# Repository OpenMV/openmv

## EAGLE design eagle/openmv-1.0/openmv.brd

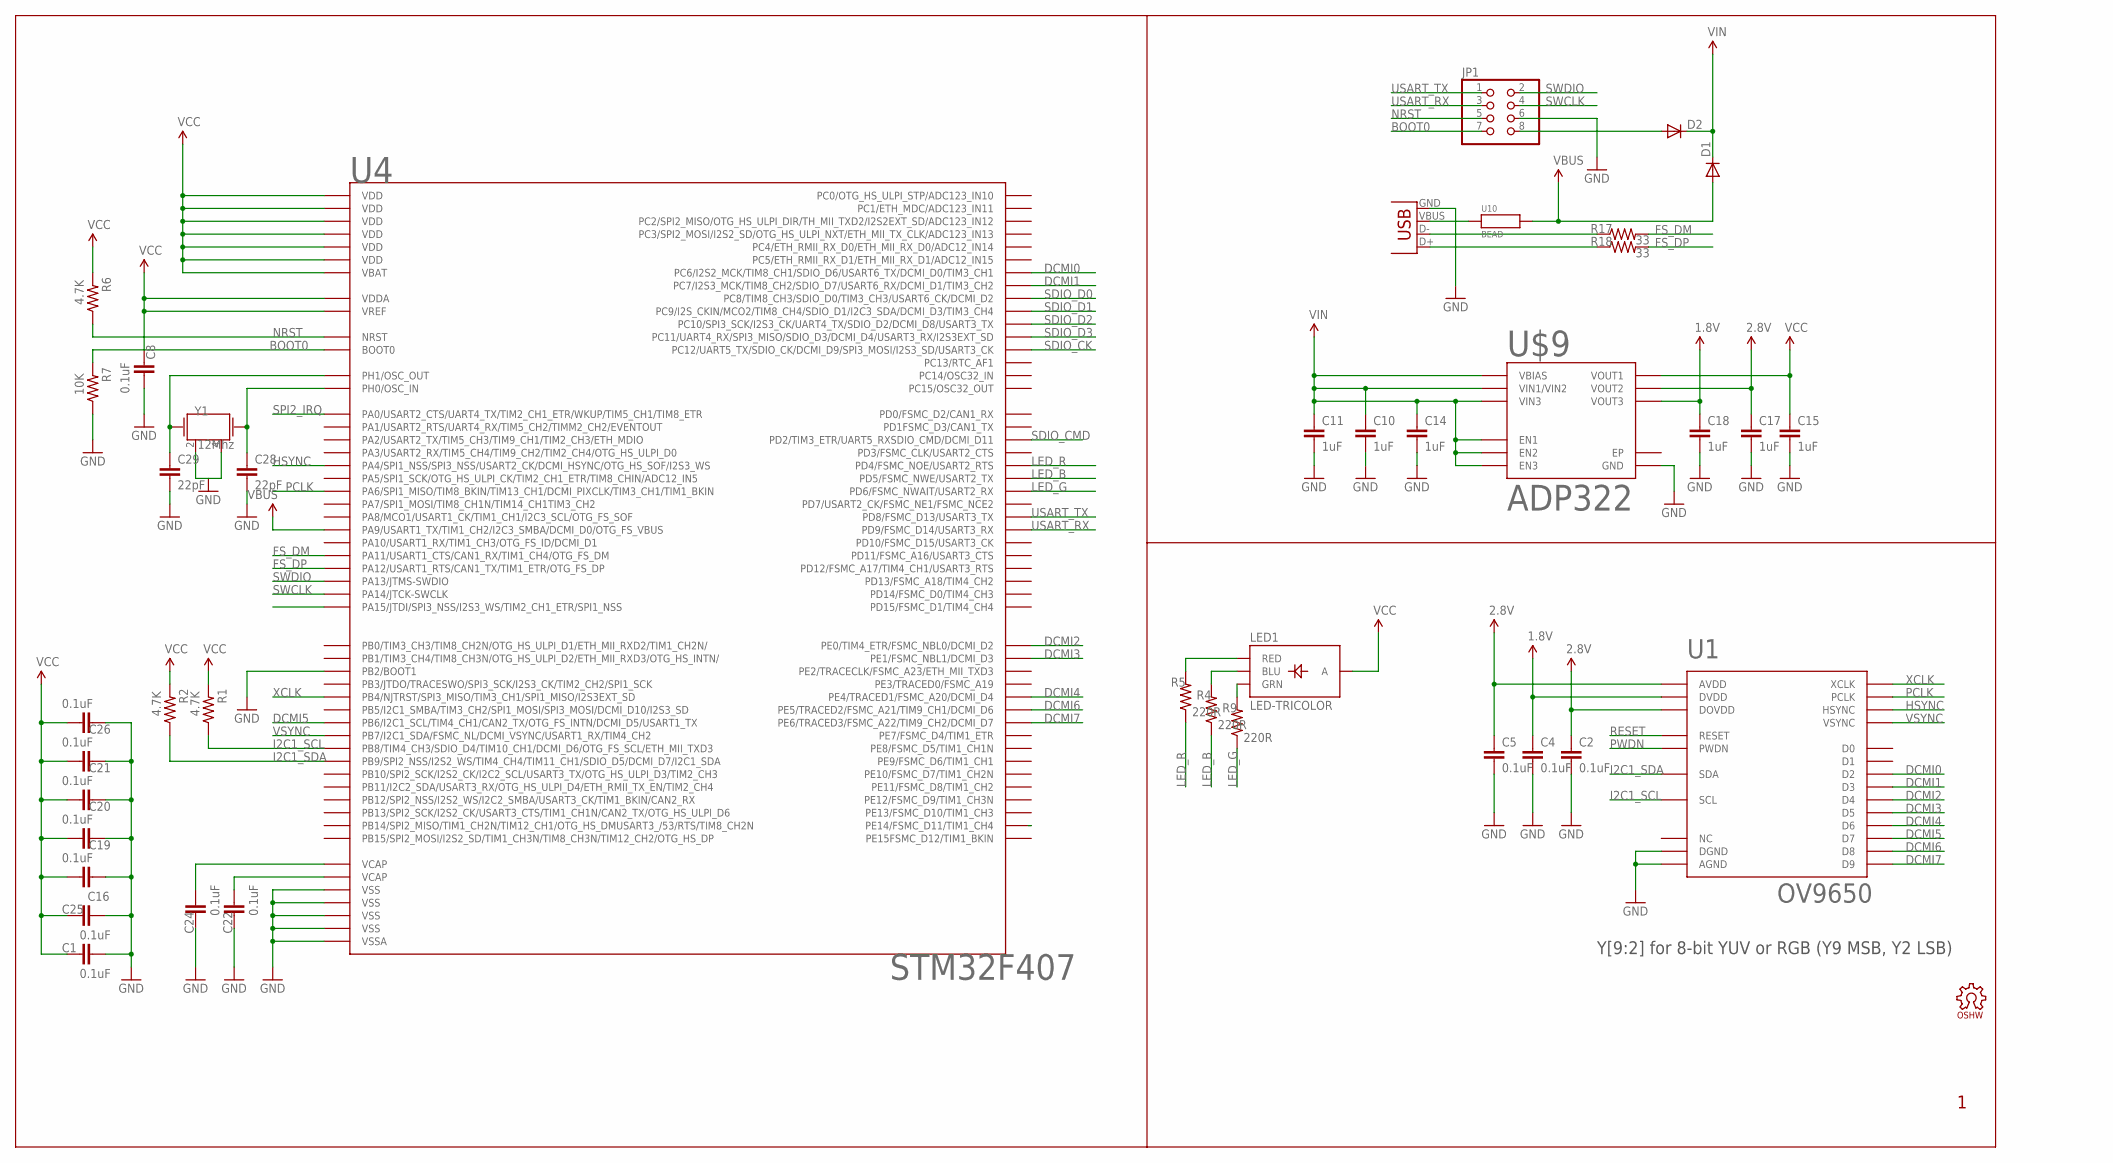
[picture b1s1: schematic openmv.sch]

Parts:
C1, C2, C4, C5, C8, C16, C19, C20, C21, C22, C24, C25, C26: 0.1uF; 0402-CAP
C10, C11, C14, C15, C17, C18: 1uF; 0402-CAP
C28, C29: 22pF; 0402-CAP
D1, D2: DIODESOD; SOD-323
JP1: PINHD-2X4; 2X04
LED1: LED-TRICOLOR; LED-TRICOLOR-SMD
LOGO2: OSHW_LOGO_FILLX0100-NT; OSHW_FILLX100_NOTEXT
R1, R2, R6: 4.7K; 0402-RES
R4, R5, R9: 220R; 0402-RES
R7: 10K; 0402-RES
R17, R18: 33; 0402-RES
U1: OV9650
U4: STM32F407; LQFP100
U10: BEAD; 0402-CAP
U$9: ADP322; WFQFN-16
X2: USB-MICROB
Y1: 12Mhz; CRYSTAL-SMD-5X3

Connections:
1.8V: C4.1, C18.1, U1.P$10 (DVDD), U$9.8 (VOUT3)
2.8V: C2.1, C5.1, C17.1, U1.P$4 (AVDD), U1.P$11 (DOVDD), U$9.6 (VOUT2)
BOOT0: JP1.7, R7.2, U4.94 (BOOT0)
DCMI0: U1.P$19 (D2), U4.63 (PC6/I2S2_MCK/TIM8_CH1/SDIO_D6/USART6_TX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)
DCMI1: U1.P$21 (D3), U4.64 (PC7/I2S3_MCK/TIM8_CH2/SDIO_D7/USART6_RX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)
DCMI2: U1.P$22 (D4), U4.97 (PE0/TIM4_ETR/FSMC_NBL0/DCMI_D2)
DCMI3: U1.P$20 (D5), U4.98 (PE1/FSMC_NBL1/DCMI_D3)
DCMI4: U1.P$18 (D6), U4.3 (PE4/TRACED1/FSMC_A20/DCMI_D4)
DCMI5: U1.P$16 (D7), U4.92 (PB6/I2C1_SCL/TIM4_CH1/CAN2_TX/OTG_FS_IN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)
DCMI6: U1.P$14 (D8), U4.4 (PE5/TRACED2/FSMC_A21/TIM9_CH1/DCMI_D6)
DCMI7: U1.P$12 (D9), U4.5 (PE6/TRACED3/FSMC_A22/TIM9_CH2/DCMI_D7)
FS_DM: R17.2, U4.70 (PA11/USART1_CTS/CAN1_RX/TIM1_CH4/OTG_FS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)
FS_DP: R18.2, U4.71 (PA12/USART1_RTS/CAN1_TX/TIM1_ETR/OTG_FS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)
GND: C1.1, C2.2, C4.2, C5.2, C8.1, C10.2, C11.2, C14.2, C15.2, C16.1, C17.2, C18.2, C19.2, C20.2, C21.2, C22.2, C24.2, C25.1, C26.2, C28.2, C29.2, JP1.6, R7.1, U1.P$2 (AGND), U1.P$15 (DGND), U4.10 (VSS), U4.20 (VSSA), U4.27 (VSS), U4.37 (PB2/BOOT1), U4.74 (VSS), U4.99 (VSS), U$9.12 (GND), X2.GND, Y1.2, Y1.4
HSYNC: U1.P$9 (HSYNC), U4.29 (PA4/SPI1_NSS/SPI3_NSS/USART2_CK/DCMI_HS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)
I2C1_SCL: R1.1, U1.P$5 (SCL), U4.95 (PB8/TIM4_CH3/SDIO_D4/TIM10_CH1/DCMI_D6/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)
I2C1_SDA: R2.1, U1.P$3 (SDA), U4.96 (PB9/SPI2_NSS/I2S2_WS/TIM4_CH4/TIM11_CH1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)
LED_B: R4.1, U4.86 (PD5/FSMC_NWE/USART2_TX)
LED_G: R9.1, U4.87 (PD6/FSMC_NWAIT/USART2_RX)
LED_R: R5.1, U4.85 (PD4/FSMC_NOE/USART2_RTS)
unnamed: D2.2 (A), JP1.8
unnamed: LED1.G (GRN), R9.2
unnamed: LED1.B (BLU), R4.2
unnamed: C29.1, U4.13 (PH1/OSC_OUT), Y1.1
unnamed: C28.1, U4.12 (PH0/OSC_IN), Y1.3 (2)
unnamed: LED1.R (RED), R5.2
unnamed: R17.1, X2.D-
unnamed: R18.1, X2.D+
unnamed: U10.1, X2.VBUS
NRST: JP1.5, R6.1, U4.14 (NRST)
PCLK: U1.P$17 (PCLK), U4.31 (PA6/SPI1_MISO/TIM8_BKIN/TIM13_CH1/DCMI_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)
PWDN: U1.P$8 (PWDN)
RESET: U1.P$6 (RESET)
SDIO_CK: U4.80 (PC12/UART5_TX/SDIO_CK/DCMI_D9/SPI3_MOSI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)
SDIO_CMD: U4.83 (PD2/TIM3_ETR/UART5_RXSDIO_CMD/DCMI_D11)
SDIO_D0: U4.65 (PC8/TIM8_CH3/SDIO_D0/TIM3_CH3/USART6_CK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)
SDIO_D1: U4.66 (PC9/I2S_CKIN/MCO2/TIM8_CH4/SDIO_D1/I2C3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)
SDIO_D2: U4.78 (PC10/SPI3_SCK/I2S3_CK/UART4_TX/SDIO_D2/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)
SDIO_D3: U4.79 (PC11/UART4_RX/SPI3_MISO/SDIO_D3/DCMI_D4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)
SPI2_IRQ: U4.23 (PA0/USART2_CTS/UART4_TX/TIM2_CH1_ETR/WK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)
SWCLK: JP1.4, U4.76 (PA14/JTCK-SWCLK)
SWDIO: JP1.2, U4.72 (PA13/JTMS-SWDIO)
USART_RX: JP1.3, U4.56 (PD9/FSMC_D14/USART3_RX)
USART_TX: JP1.1, U4.55 (PD8/FSMC_D13/USART3_TX)
VBUS: D1.2 (A), U4.68 (PA9/USART1_TX/TIM1_CH2/I2C3_SMBA/DCMI_D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), U10.2
VCAP1: C24.1, U4.49 (VCAP)
VCAP2: C22.1, U4.73 (VCAP)
VCC: C1.2, C8.2, C15.1, C16.2, C19.1, C20.1, C21.1, C25.2, C26.1, LED1.A, R1.2, R2.2, R6.2, U4.6 (VBAT), U4.11 (VDD), U4.19 (VDD), U4.21 (VREF), U4.22 (VDDA), U4.28 (VDD), U4.50 (VDD), U4.75 (VDD), U4.100 (VDD), U$9.5 (VOUT1)
VIN: C10.1, C11.1, C14.1, D1.1 (C), D2.1 (C), U$9.1 (EN1), U$9.2 (VBIAS), U$9.3 (VIN1/VIN2), U$9.10 (VIN3), U$9.15 (EN3), U$9.16 (EN2)
VSYNC: U1.P$7 (VSYNC), U4.93 (PB7/I2C1_SDA/FSMC_NL/DCMI_VSYNC/USART1_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)
XCLK: U1.P$13 (XCLK), U4.90 (PB4/NJTRST/SPI3_MISO/TIM3_CH1/SPI1_MISO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)

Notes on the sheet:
Y[9:2] for 8-bit YUV or RGB (Y9 MSB, Y2 LSB)

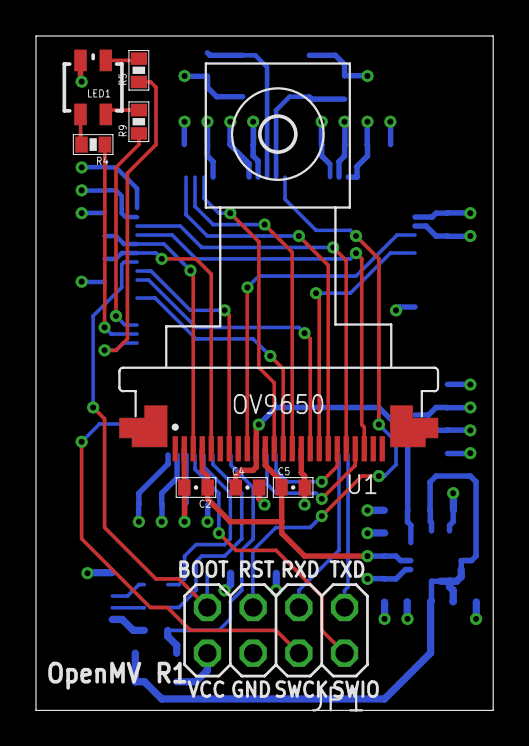
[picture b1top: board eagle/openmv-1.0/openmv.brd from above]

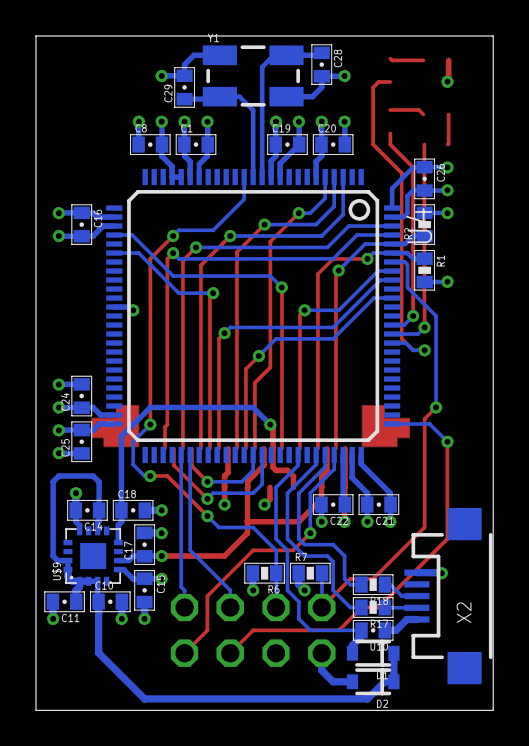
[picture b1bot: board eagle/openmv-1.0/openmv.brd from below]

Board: 4 copper layers, 25.4 x 37.5 mm, 41 parts (31 on the bottom side), 42 nets.

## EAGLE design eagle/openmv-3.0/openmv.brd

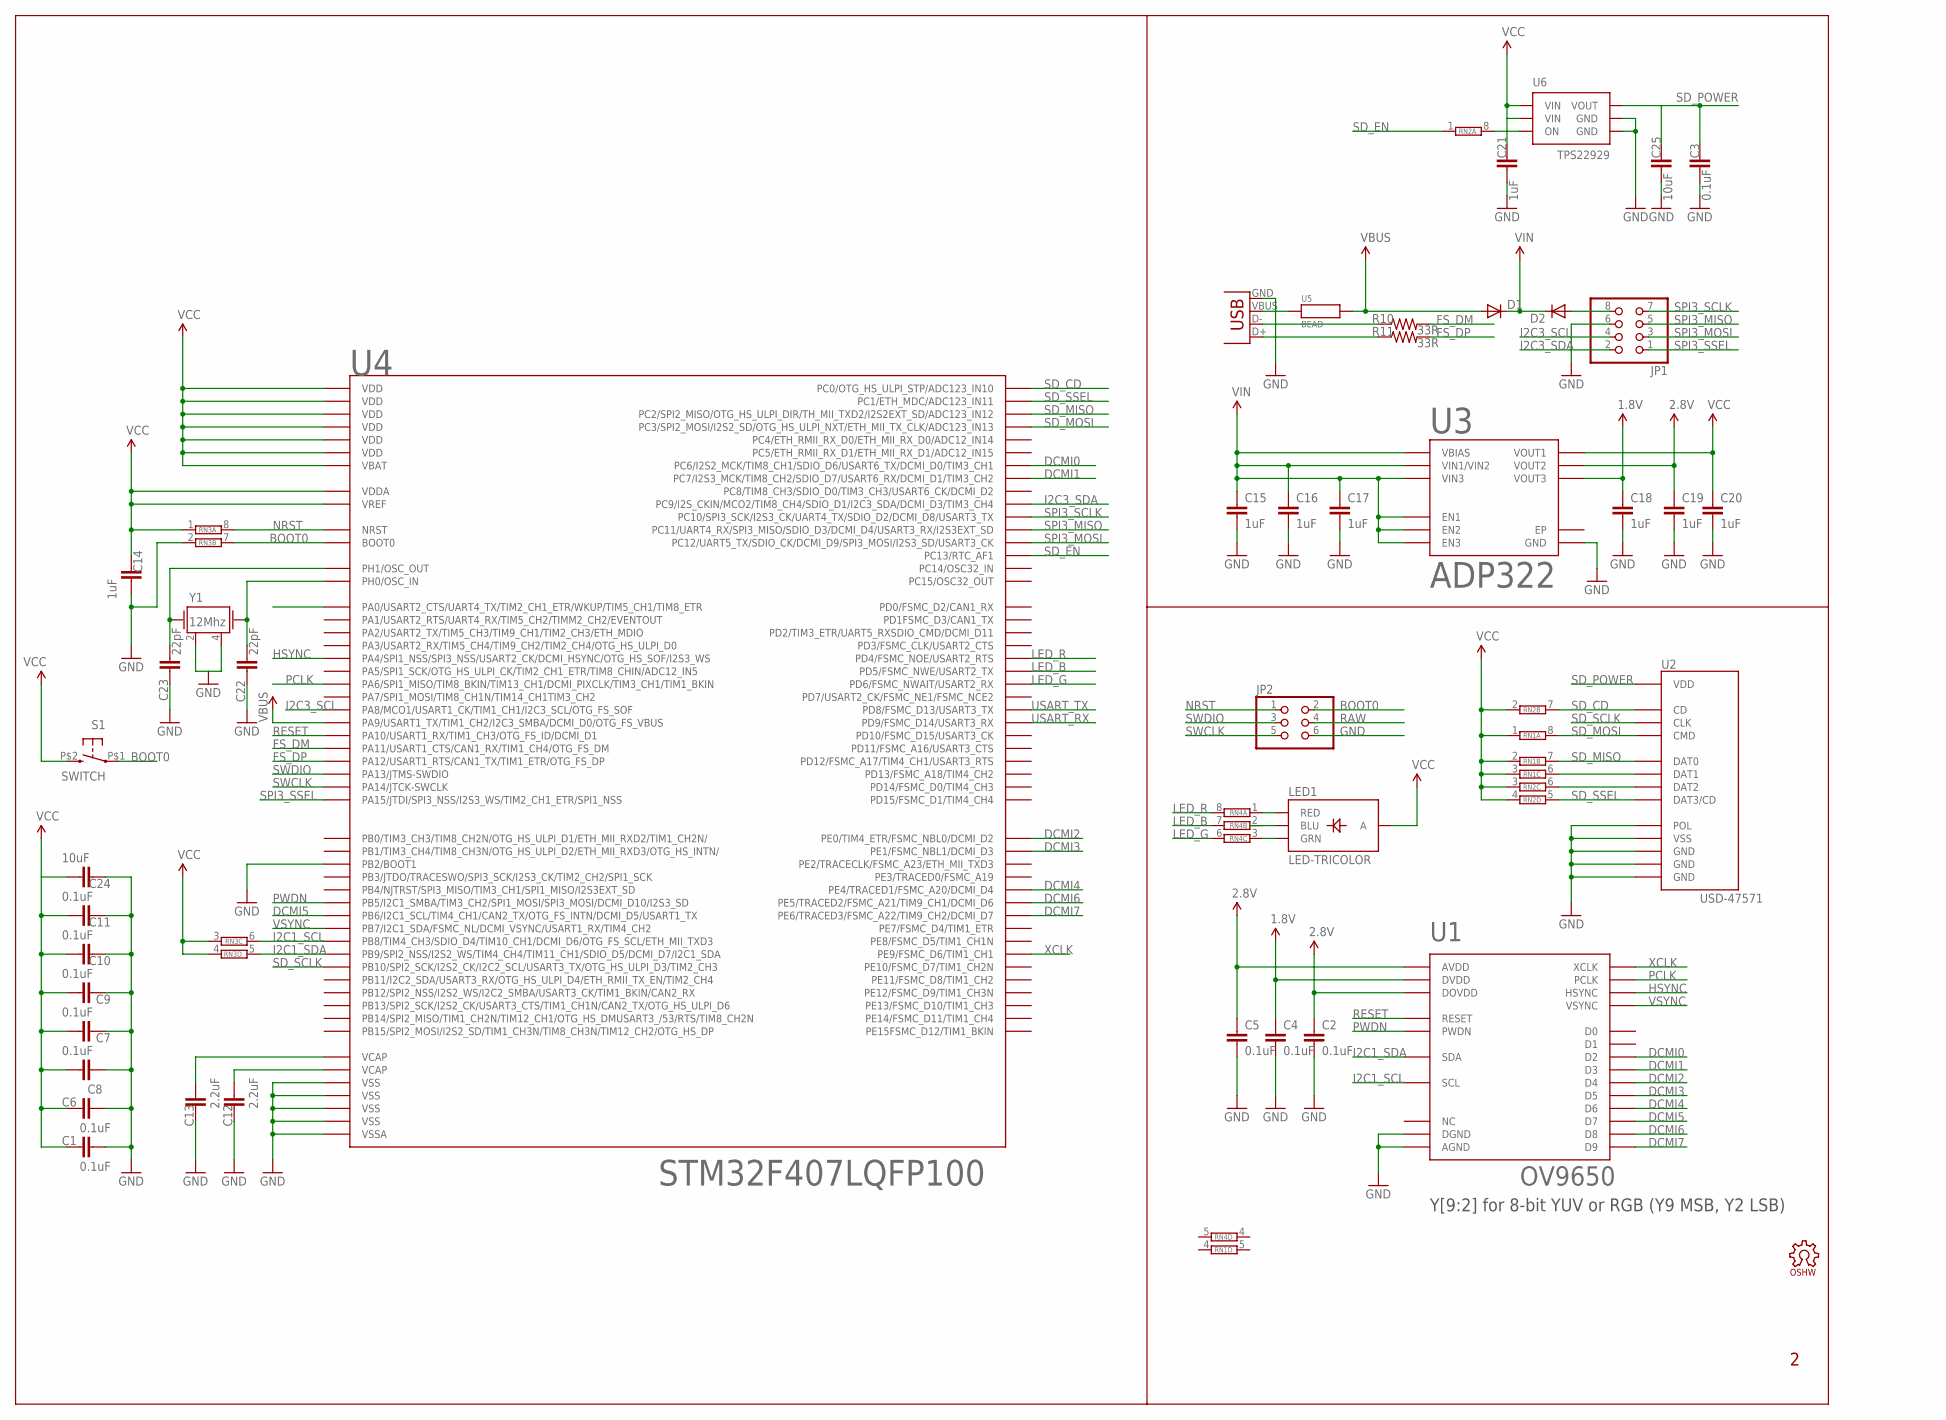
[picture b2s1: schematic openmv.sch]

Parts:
C1, C2, C3, C4, C5, C6, C7, C8, C9, C10, C11: 0.1uF; 0402-CAP
C12, C13: 2.2uF; 0402-CAP
C14, C15, C16, C17, C18, C19, C20, C21: 1uF; 0402-CAP
C22, C23: 22pF; 0402-CAP
C24, C25: 10uF; 0805
D1, D2: DIODESOD; SOD-323
JP1: PINHD-2X4; 2X04
JP2: PINHD-2X3; 2X03
LED1: LED-TRICOLOR; LED-TRICOLOR-SMD
LOGO1: OSHW_LOGO_FILLX0150-NT; OSHW_FILLX150_NOTEXT
R10, R11: 33R; 0402-RES
RN1, RN2, RN3, RN4: 4R-NCAT16; CAT16
S1: SWITCH; B3U-1000P
U1: OV9650
U2: USD-47571
U3: ADP322; WFQFN-16
U4: STM32F407LQFP100; LQFP100
U5: BEAD; 0402-CAP
U6: TPS22929; SOT23-6
X1: USB-MICROB
Y1: 12Mhz; CRYSTAL-SMD-5X3

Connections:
1.8V: C4.1, C18.1, U1.P$10 (DVDD), U3.8 (VOUT3)
2.8V: C2.1, C5.1, C19.1, U1.P$4 (AVDD), U1.P$11 (DOVDD), U3.6 (VOUT2)
BOOT0: JP2.2, RN3.7 (2), S1.P$1 (1), U4.94 (BOOT0)
DCMI0: U1.P$19 (D2), U4.63 (PC6/I2S2_MCK/TIM8_CH1/SDIO_D6/USART6_TX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)
DCMI1: U1.P$21 (D3), U4.64 (PC7/I2S3_MCK/TIM8_CH2/SDIO_D7/USART6_RX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)
DCMI2: U1.P$22 (D4), U4.97 (PE0/TIM4_ETR/FSMC_NBL0/DCMI_D2)
DCMI3: U1.P$20 (D5), U4.98 (PE1/FSMC_NBL1/DCMI_D3)
DCMI4: U1.P$18 (D6), U4.3 (PE4/TRACED1/FSMC_A20/DCMI_D4)
DCMI5: U1.P$16 (D7), U4.92 (PB6/I2C1_SCL/TIM4_CH1/CAN2_TX/OTG_FS_IN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)
DCMI6: U1.P$14 (D8), U4.4 (PE5/TRACED2/FSMC_A21/TIM9_CH1/DCMI_D6)
DCMI7: U1.P$12 (D9), U4.5 (PE6/TRACED3/FSMC_A22/TIM9_CH2/DCMI_D7)
FS_DM: R10.2, U4.70 (PA11/USART1_CTS/CAN1_RX/TIM1_CH4/OTG_FS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)
FS_DP: R11.2, U4.71 (PA12/USART1_RTS/CAN1_TX/TIM1_ETR/OTG_FS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)
GND: C1.1, C2.2, C3.2, C4.2, C5.2, C6.1, C7.2, C8.1, C9.2, C10.2, C11.2, C12.2, C13.2, C14.1, C15.2, C16.2, C17.2, C18.2, C19.2, C20.2, C21.2, C22.2, C23.2, C24.1, C25.2, JP1.6, JP2.6, RN3.2 (1), U1.P$2 (AGND), U1.P$15 (DGND), U2.G$1 (GND), U2.G$2 (GND), U2.G$3 (GND), U2.G$4 (POL), U2.P$6 (VSS), U3.12 (GND), U4.10 (VSS), U4.20 (VSSA), U4.27 (VSS), U4.37 (PB2/BOOT1), U4.74 (VSS), U4.99 (VSS), U6.2 (GND), U6.5 (GND), X1.GND, Y1.2, Y1.4
HSYNC: U1.P$9 (HSYNC), U4.29 (PA4/SPI1_NSS/SPI3_NSS/USART2_CK/DCMI_HS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)
I2C1_SCL: RN3.6 (2), U1.P$5 (SCL), U4.95 (PB8/TIM4_CH3/SDIO_D4/TIM10_CH1/DCMI_D6/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)
I2C1_SDA: RN3.5 (2), U1.P$3 (SDA), U4.96 (PB9/SPI2_NSS/I2S2_WS/TIM4_CH4/TIM11_CH1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)
I2C3_SCL: JP1.4, U4.67 (PA8/MCO1/USART1_CK/TIM1_CH1/I2C3_SCL/OT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)
I2C3_SDA: JP1.2, U4.66 (PC9/I2S_CKIN/MCO2/TIM8_CH4/SDIO_D1/I2C3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)
LED_B: RN4.7 (2), U4.86 (PD5/FSMC_NWE/USART2_TX)
LED_G: RN4.6 (2), U4.87 (PD6/FSMC_NWAIT/USART2_RX)
LED_R: RN4.8 (2), U4.85 (PD4/FSMC_NOE/USART2_RTS)
unnamed: RN1.6 (2), U2.P$8 (DAT1)
unnamed: RN2.6 (2), U2.P$1 (DAT2)
unnamed: LED1.R (RED), RN4.1
unnamed: LED1.B (BLU), RN4.2 (1)
unnamed: LED1.G (GRN), RN4.3 (1)
unnamed: RN2.8 (2), U6.3 (ON)
unnamed: C23.1, U4.13 (PH1/OSC_OUT), Y1.1
unnamed: C22.1, U4.12 (PH0/OSC_IN), Y1.3 (2)
unnamed: R10.1, X1.D-
unnamed: R11.1, X1.D+
unnamed: U5.1, X1.VBUS
NRST: JP2.1, RN3.8 (2), U4.14 (NRST)
PCLK: U1.P$17 (PCLK), U4.31 (PA6/SPI1_MISO/TIM8_BKIN/TIM13_CH1/DCMI_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)
PWDN: U1.P$8 (PWDN), U4.91 (PB5/I2C1_SMBA/TIM3_CH2/SPI1_MOSI/SPI3_M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)
RAW: D2.2 (A), JP1.8, JP2.4
RESET: U1.P$6 (RESET), U4.69 (PA10/USART1_RX/TIM1_CH3/OTG_FS_ID/DCMI_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)
SD_CD: RN2.7 (2), U2.G$5 (CD), U4.15 (PC0/OTG_HS_ULPI_STP/ADC123_IN10)
SD_EN: RN2.1, U4.7 (PC13/RTC_AF1)
SD_MISO: RN1.7 (2), U2.P$7 (DAT0), U4.17 (PC2/SPI2_MISO/OTG_HS_ULPI_DIR/TH_MII_TX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)
SD_MOSI: RN1.8 (2), U2.P$3 (CMD), U4.18 (PC3/SPI2_MOSI/I2S2_SD/OTG_HS_ULPI_NXT/E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)
SD_POWER: C3.1, C25.1, U2.P$4 (VDD), U6.1 (VOUT)
SD_SCLK: U2.P$5 (CLK), U4.47 (PB10/SPI2_SCK/I2S2_CK/I2C2_SCL/USART3_T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)
SD_SSEL: RN2.5 (2), U2.P$2 (DAT3/CD), U4.16 (PC1/ETH_MDC/ADC123_IN11)
SPI3_MISO: JP1.5, U4.79 (PC11/UART4_RX/SPI3_MISO/SDIO_D3/DCMI_D4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)
SPI3_MOSI: JP1.3, U4.80 (PC12/UART5_TX/SDIO_CK/DCMI_D9/SPI3_MOSI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)
SPI3_SCLK: JP1.7, U4.78 (PC10/SPI3_SCK/I2S3_CK/UART4_TX/SDIO_D2/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)
SPI3_SSEL: JP1.1, U4.77 (PA15/JTDI/SPI3_NSS/I2S3_WS/TIM2_CH1_ETR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)
SWCLK: JP2.5, U4.76 (PA14/JTCK-SWCLK)
SWDIO: JP2.3, U4.72 (PA13/JTMS-SWDIO)
USART_RX: U4.56 (PD9/FSMC_D14/USART3_RX)
USART_TX: U4.55 (PD8/FSMC_D13/USART3_TX)
VBUS: D1.2 (A), U4.68 (PA9/USART1_TX/TIM1_CH2/I2C3_SMBA/DCMI_D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), U5.2
VCAP1: C13.1, U4.49 (VCAP)
VCAP2: C12.1, U4.73 (VCAP)
VCC: C1.2, C6.2, C7.1, C8.2, C9.1, C10.1, C11.1, C14.2, C20.1, C21.1, C24.2, LED1.A, RN1.1, RN1.2 (1), RN1.3 (1), RN2.2 (1), RN2.3 (1), RN2.4 (1), RN3.1, RN3.3 (1), RN3.4 (1), S1.P$2 (2), U3.5 (VOUT1), U4.6 (VBAT), U4.11 (VDD), U4.19 (VDD), U4.21 (VREF), U4.22 (VDDA), U4.28 (VDD), U4.50 (VDD), U4.75 (VDD), U4.100 (VDD), U6.4 (VIN), U6.6 (VIN)
VIN: C15.1, C16.1, C17.1, D1.1 (C), D2.1 (C), U3.1 (EN1), U3.2 (VBIAS), U3.3 (VIN1/VIN2), U3.10 (VIN3), U3.15 (EN3), U3.16 (EN2)
VSYNC: U1.P$7 (VSYNC), U4.93 (PB7/I2C1_SDA/FSMC_NL/DCMI_VSYNC/USART1_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)
XCLK: U1.P$13 (XCLK), U4.40 (PE9/FSMC_D6/TIM1_CH1)

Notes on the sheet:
Y[9:2] for 8-bit YUV or RGB (Y9 MSB, Y2 LSB)

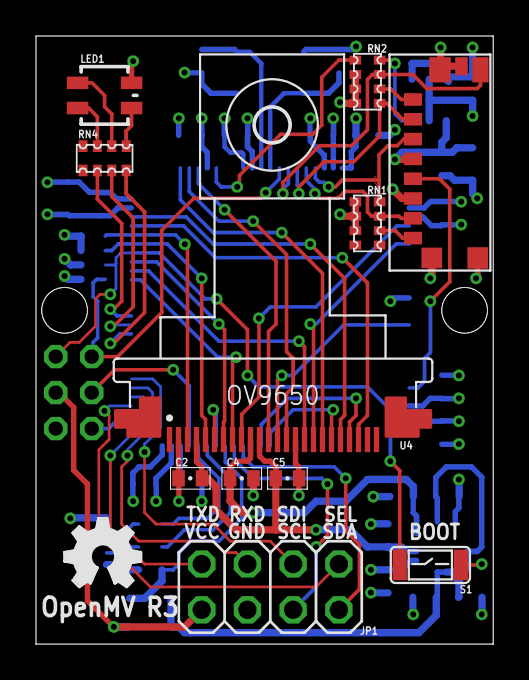
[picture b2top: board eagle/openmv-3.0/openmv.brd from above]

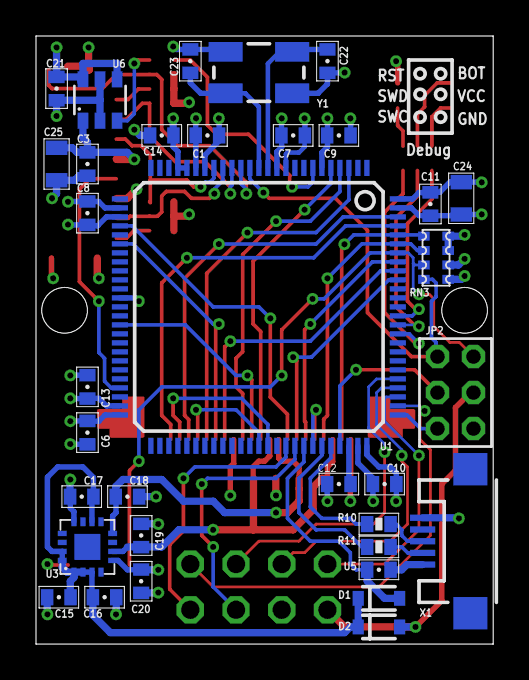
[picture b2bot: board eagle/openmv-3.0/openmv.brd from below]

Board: 4 copper layers, 25.4 x 33.8 mm, 46 parts (34 on the bottom side), 58 nets.

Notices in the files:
eagle/openmv-1.0/openmv.sch:
Copyright (c) 2013 Ibrahim Abd Elkader
This work is licensed under the Creative Commons Attribution-ShareAlike 3.0 License.
To view a copy of this license, visit http://creativecommons.org/licenses/by-sa/3.0
